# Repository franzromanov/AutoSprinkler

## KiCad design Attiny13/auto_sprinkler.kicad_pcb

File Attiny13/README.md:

auto_sprinkler_t13_V.0.1

this is the official first version of auto sprinkler with attiny13 as it's controller.

*features*

-this machine has two operation modes (timer mode & sensor mode)

-timer mode: activated every 3 hours

-sensor mode: activated when soil is dry

-max supply voltage: 12V

-costumizable motor speed using potentiometer

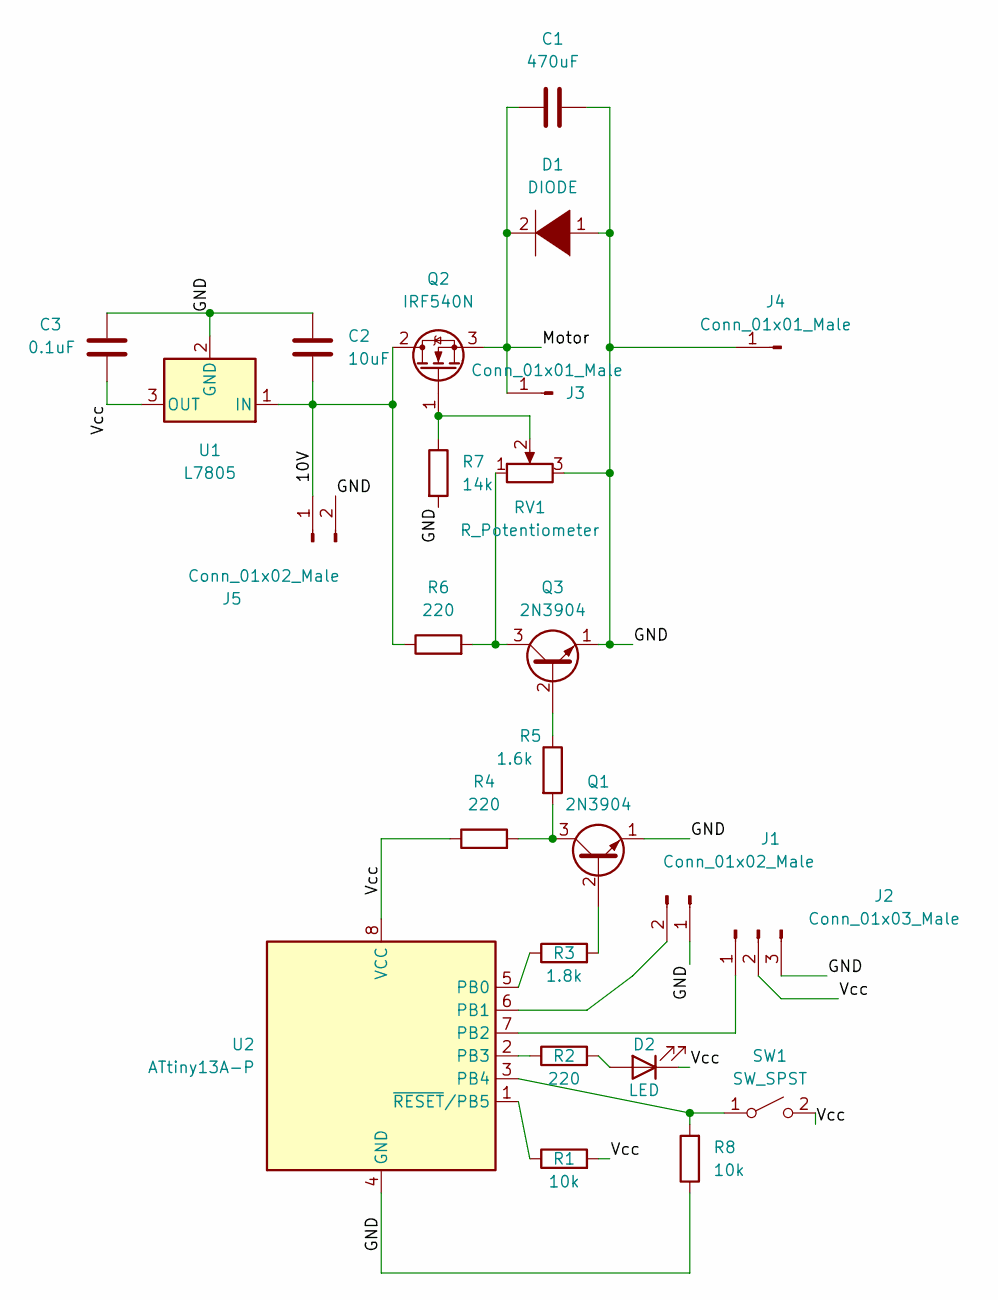
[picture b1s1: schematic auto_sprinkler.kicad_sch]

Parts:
C1: 470uF; CP_Radial_D12.5mm_P7.50mm
C2: 10uF; CP_Radial_D5.0mm_P2.50mm
C3: 0.1uF; C_Disc_D6.0mm_W4.4mm_P5.00mm
D1: DIODE; D_T-1_P5.08mm_Horizontal
D2: LED; LED_D3.0mm
J1: Conn_01x02_Male; PinHeader_1x02_P2.54mm_Vertical
J2: Conn_01x03_Male; PinHeader_1x03_P2.54mm_Vertical
J3, J4: Conn_01x01_Male; PinHeader_1x01_P2.54mm_Vertical
J5: Conn_01x02_Male; BarrelJack_Wuerth_6941xx301002
Q1, Q3: 2N3904; TO-92_Inline
Q2: IRF540N; TO-220-3_Vertical
R1, R8: 10k; R_Axial_DIN0204_L3.6mm_D1.6mm_P2.54mm_Vertical
R2, R4, R6: 220; R_Axial_DIN0204_L3.6mm_D1.6mm_P2.54mm_Vertical
R3: 1.8k; R_Axial_DIN0204_L3.6mm_D1.6mm_P2.54mm_Vertical
R5: 1.6k; R_Axial_DIN0204_L3.6mm_D1.6mm_P2.54mm_Vertical
R7: 14k; R_Axial_DIN0204_L3.6mm_D1.6mm_P2.54mm_Vertical
RV1: R_Potentiometer; Potentiometer_Vishay_148-149_Single_Horizontal
SW1: SW_SPST; SW_PUSH_6mm_H5mm
U1: L7805; TO-220-3_Vertical
U2: ATtiny13A-P; DIP-8_W7.62mm

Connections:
/10V: C2.2, J5.1, Q2.2 (D), R6.1, U1.1 (IN)
/GND: C1.2, C2.1, C3.2, D1.1 (K), J1.1, J2.3, J4.1, J5.2, Q1.1 (E), Q3.1 (E), R7.2, R8.1, RV1.3, U1.2 (GND), U2.4 (GND)
/Motor: C1.1, D1.2 (A), J3.1, Q2.3 (S)
/Vcc: C3.1, D2.1 (K), J2.2, R1.2, R4.1, SW1.2 (B), U1.3 (OUT), U2.8 (VCC)
unnamed: D2.2 (A), R2.2
unnamed: J1.2, U2.6 (PB1)
unnamed: J2.1, U2.7 (PB2)
unnamed: Q1.2 (B), R3.2
unnamed: Q1.3 (C), R4.2, R5.2
unnamed: Q2.1 (G), R7.1, RV1.2
unnamed: Q3.2 (B), R5.1
unnamed: Q3.3 (C), R6.2, RV1.1
unnamed: R1.1, U2.1 (~RESET/PB5)
unnamed: R2.1, U2.2 (PB3)
unnamed: R3.1, U2.5 (PB0)
unnamed: R8.2, SW1.1 (A), U2.3 (PB4)

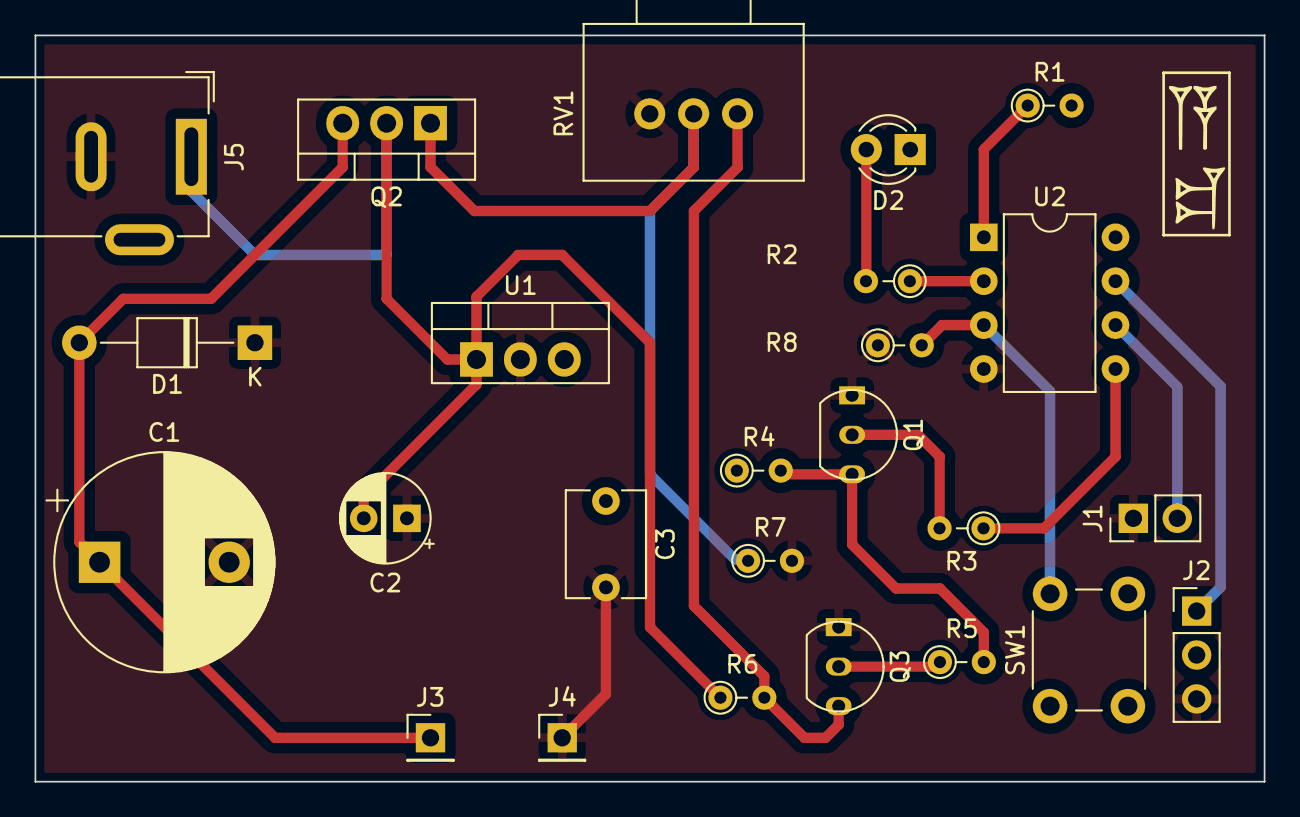
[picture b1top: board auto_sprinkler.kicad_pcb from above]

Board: 2 copper layers, 71.1 x 43.2 mm, 25 parts (0 on the bottom side), 16 nets.

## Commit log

2025-12-03 Add initial documentation for auto sprinkler project
    This document outlines the features and operation modes of the auto sprinkler system using the ATtiny13 microcontroller.
2025-12-03 Update README with project description and features
2025-12-03 Fix grammatical error in README.md
